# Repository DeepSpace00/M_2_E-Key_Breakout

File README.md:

# M_2_E-Key_Breakout
Breakout Board for I2C/UART/USB on M.2 E-Key cards

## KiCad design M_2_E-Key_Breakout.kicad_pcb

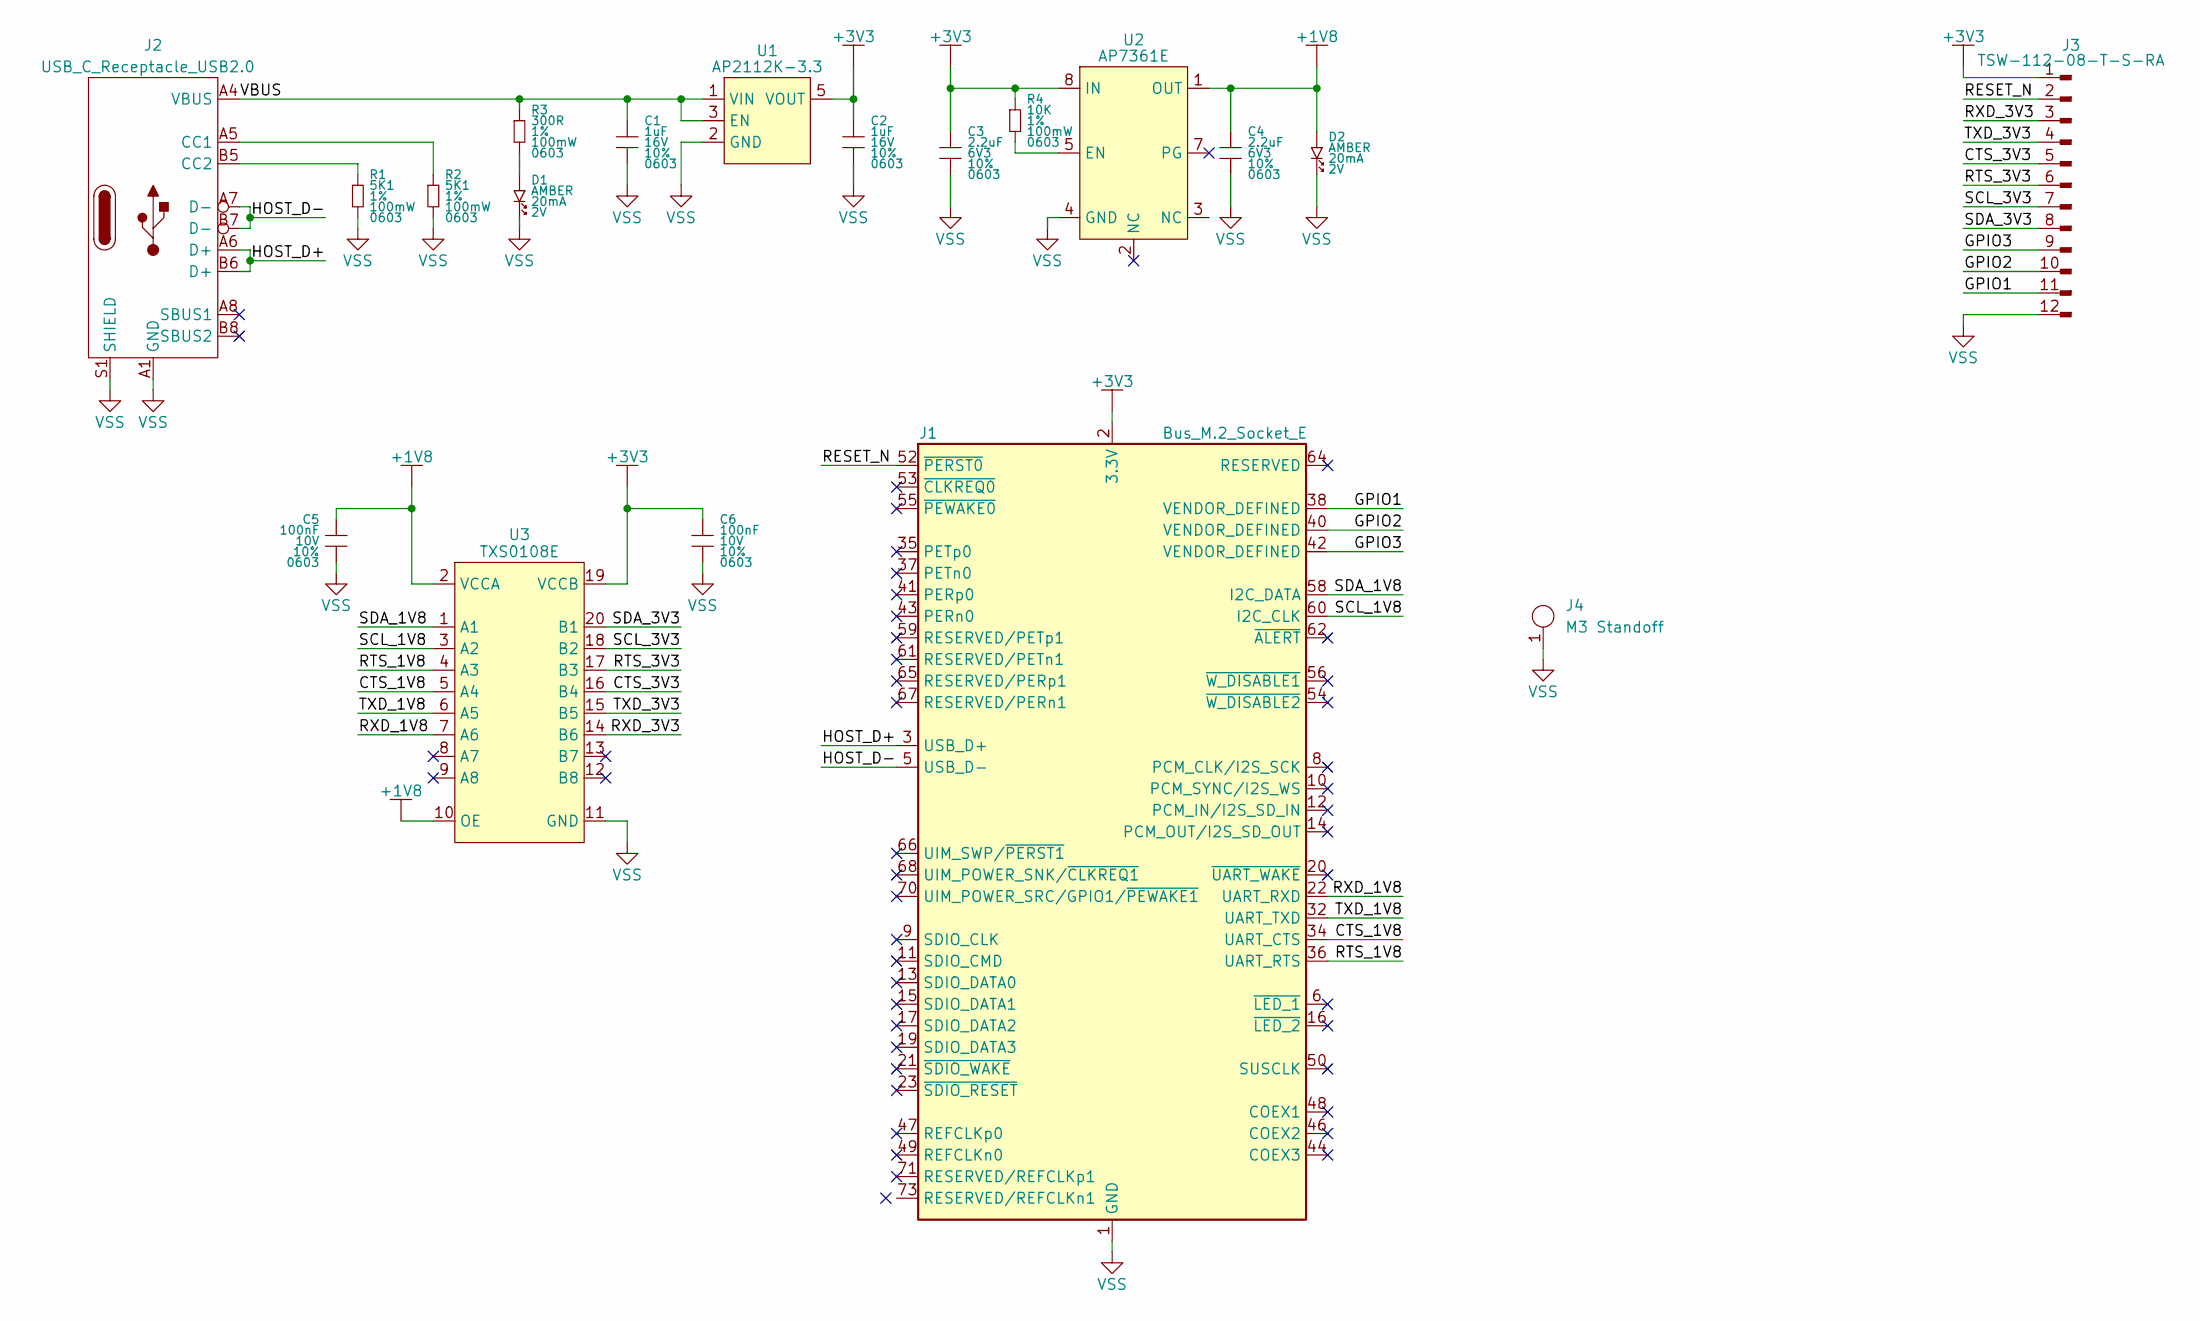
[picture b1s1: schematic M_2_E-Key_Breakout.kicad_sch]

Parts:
C1, C2: 1uF; MLCC0603; Tolerance 10%; Voltage Rating 16V; MPN KAM15AR71C105KT
C3, C4: 2.2uF; MLCC0603; Tolerance 10%; Voltage Rating 6V3; MPN KAM15AR70J225KT
C5, C6: 100nF; MLCC0603; Tolerance 10%; Voltage Rating 10V; MPN KAM15AR71A104KT
D1, D2: LTST-C190KYKT; LTST-0603; Forward Voltage 2V; MPN LTST-C190KYKT
J1: Bus_M.2_Socket_E; MDT420E01001
J2: USB_C_Receptacle_USB2.0; MOLEX_2171790001
J3: TSW-112-08-T-S-RA; conn_01x12_254_right_angle; MPN TSW-112-08-T-S-RA
J4: M3 Standoff; 9775031360R; MPN 9775041360R
R1, R2: 5K1; CRCW0603; Tolerance 1%; Power Rating 100mW; MPN CRCW06035K10FKEA
R3: 300R; CRCW0603; Tolerance 1%; Power Rating 100mW; MPN CRCW0603300RFKEA
R4: 10K; CRCW0603; Tolerance 1%; Power Rating 100mW; MPN CRCW060310K0FKEA
U1: AP2112K-3.3; SOT23-5P95_280X300X110L40X38N; MPN AP2112K-3.3TRG1
U2: AP7361E; UDFN8P65_300X300X60L25X45L; MPN AP7361E-18FGE-7
U3: TXS0108E; RGY0020A; MPN TXS0108ERGYR

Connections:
+1V8: C4.1, C5.1, D2.1, U2.1 (OUT), U3.2 (VCCA), U3.10 (OE)
+3V3: C2.1, C3.1, C6.1, J1.2 (3.3V), J1.4 (3.3V), J1.72 (3.3V), J1.74 (3.3V), J3.1, R4.1, U1.5 (VOUT), U2.8 (IN), U3.19 (VCCB)
/CTS_1V8: J1.34 (UART_CTS), U3.5 (A4)
/CTS_3V3: J3.5, U3.16 (B4)
/GPIO1: J1.38 (VENDOR_DEFINED), J3.11
/GPIO2: J1.40 (VENDOR_DEFINED), J3.10
/GPIO3: J1.42 (VENDOR_DEFINED), J3.9
/HOST_D+: J1.3 (USB_D+), J2.A6 (D+), J2.B6 (D+)
/HOST_D-: J1.5 (USB_D-), J2.A7 (D-), J2.B7 (D-)
/RESET_N: J1.52 (~PERST0), J3.2
/RTS_1V8: J1.36 (UART_RTS), U3.4 (A3)
/RTS_3V3: J3.6, U3.17 (B3)
/RXD_1V8: J1.22 (UART_RXD), U3.7 (A6)
/RXD_3V3: J3.3, U3.14 (B6)
/SCL_1V8: J1.60 (I2C_CLK), U3.3 (A2)
/SCL_3V3: J3.7, U3.18 (B2)
/SDA_1V8: J1.58 (I2C_DATA), U3.1 (A1)
/SDA_3V3: J3.8, U3.20 (B1)
/TXD_1V8: J1.32 (UART_TXD), U3.6 (A5)
/TXD_3V3: J3.4, U3.15 (B5)
/VBUS: C1.1, J2.A4 (VBUS), J2.A9 (VBUS), J2.B4 (VBUS), J2.B9 (VBUS), R3.1, U1.1 (VIN), U1.3 (EN)
unnamed: D1.1, R3.2
unnamed: J2.A5 (CC1), R2.1
unnamed: J2.B5 (CC2), R1.1
unnamed: R4.2, U2.5 (EN)
VSS: C1.2, C2.2, C3.2, C4.2, C5.2, C6.2, D1.2, D2.2, J1.1 (GND), J1.7 (GND), J1.18 (GND), J1.33 (GND), J1.39 (GND), J1.45 (GND), J1.51 (GND), J1.57 (GND), J1.63 (GND), J1.69 (GND), J1.75 (GND), J2.A1 (GND), J2.A12 (GND), J2.B1 (GND), J2.B12 (GND), J2.S1 (SHIELD), J3.12, J4.1, R1.2, R2.2, U1.2 (GND), U2.4 (GND), U2.9 (GND), U3.11 (GND), U3.21 (PGND)

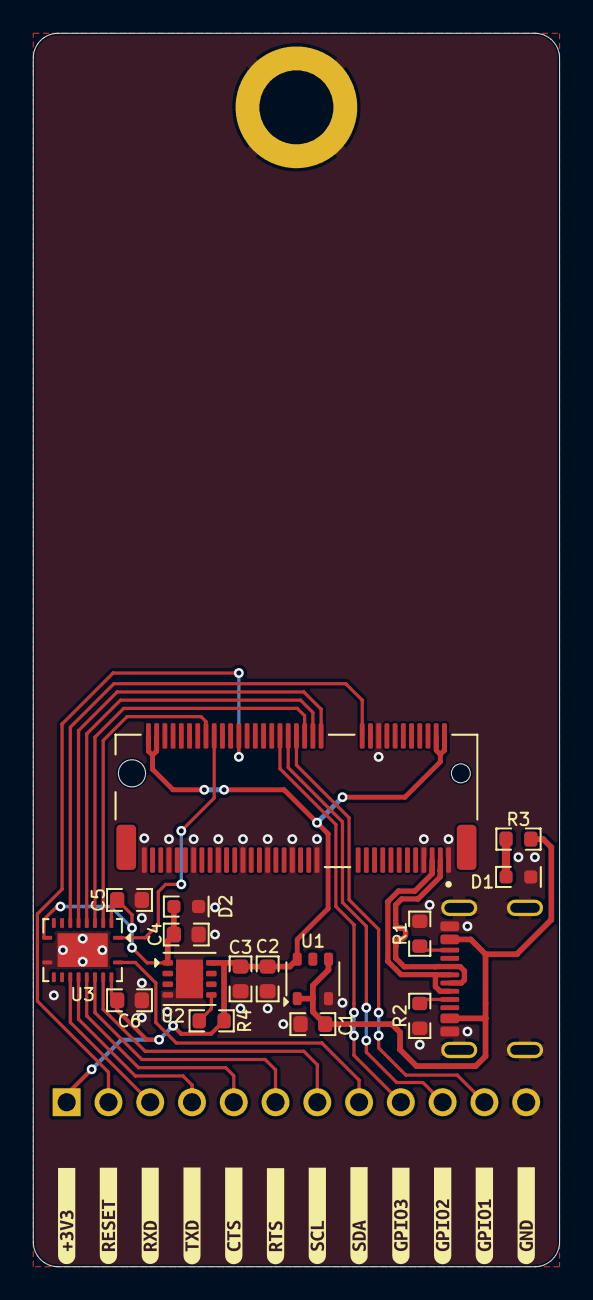
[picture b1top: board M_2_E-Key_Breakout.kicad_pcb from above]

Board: 2 copper layers, 32.0 x 75.0 mm, 31 parts (0 on the bottom side), 26 nets.

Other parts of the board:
kibuzzard-67992A70: G***; kibuzzard-67992A70
kibuzzard-67992A99: G***; kibuzzard-67992A99
kibuzzard-67992AB6: G***; kibuzzard-67992AB6
kibuzzard-67992AD3: G***; kibuzzard-67992AD3
kibuzzard-67992ADA: G***; kibuzzard-67992ADA
kibuzzard-67992AE8: G***; kibuzzard-67992AE8
kibuzzard-67992AF4: G***; kibuzzard-67992AF4
kibuzzard-67992B5F: G***; kibuzzard-67992B5F
kibuzzard-67992B6A: G***; kibuzzard-67992B6A
kibuzzard-67992B31: G***; kibuzzard-67992B31
kibuzzard-67992B48: G***; kibuzzard-67992B48
kibuzzard-679928CE: G***; kibuzzard-679928CE
